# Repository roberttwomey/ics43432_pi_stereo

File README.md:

# ics43432_pi_stereo
stereo i2s mems mic for raspberry pi using ics43432

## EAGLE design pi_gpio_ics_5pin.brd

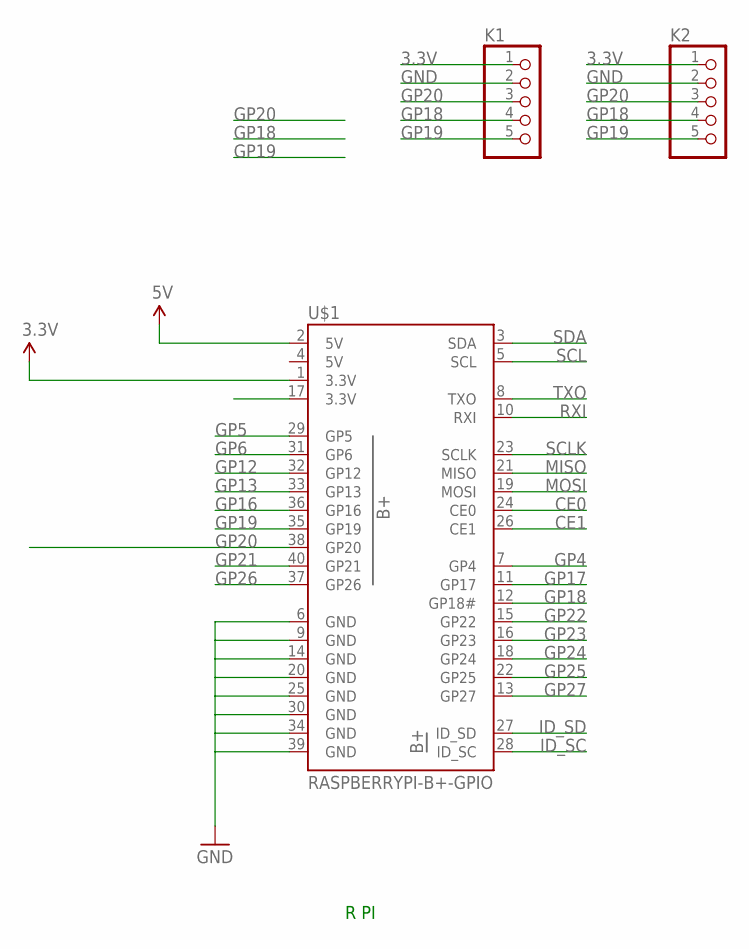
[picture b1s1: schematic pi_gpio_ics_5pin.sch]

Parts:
K1, K2: HEADER-1X5SMT; 1X05_SMT
U$1: RASPBERRYPI-B+-GPIO; 2X20-SHROUDED

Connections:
3.3V: K1.1, K2.1, U$1.1 (3.3V), U$1.17 (3.3V)
5V: U$1.2 (5V), U$1.4 (5V)
CE0: U$1.24 (CE0)
CE1: U$1.26 (CE1)
GND: K1.2, K2.2, U$1.6 (GND), U$1.9 (GND), U$1.14 (GND), U$1.20 (GND), U$1.25 (GND), U$1.30 (GND), U$1.34 (GND), U$1.39 (GND)
GP4: U$1.7 (GP4)
GP5: U$1.29 (GP5)
GP6: U$1.31 (GP6)
GP12: U$1.32 (GP12)
GP13: U$1.33 (GP13)
GP16: U$1.36 (GP16)
GP17: U$1.11 (GP17)
GP18: K1.4, K2.4, U$1.12 (GP18#)
GP19: K1.5, K2.5, U$1.35 (GP19)
GP20: K1.3, K2.3, U$1.38 (GP20)
GP21: U$1.40 (GP21)
GP22: U$1.15 (GP22)
GP23: U$1.16 (GP23)
GP24: U$1.18 (GP24)
GP25: U$1.22 (GP25)
GP26: U$1.37 (GP26)
GP27: U$1.13 (GP27)
ID_SC: U$1.28 (ID_SC)
ID_SD: U$1.27 (ID_SD)
MISO: U$1.21 (MISO)
MOSI: U$1.19 (MOSI)
RXI: U$1.10 (RXI)
SCL: U$1.5 (SCL)
SCLK: U$1.23 (SCLK)
SDA: U$1.3 (SDA)
TXO: U$1.8 (TXO)

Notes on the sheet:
R PI

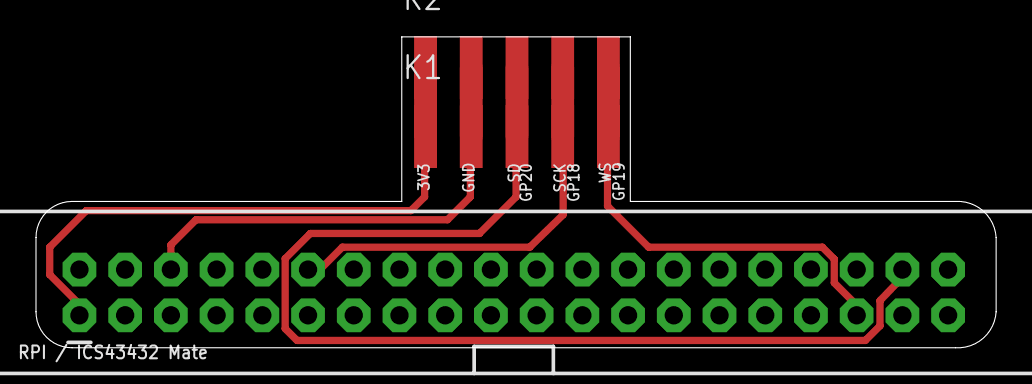
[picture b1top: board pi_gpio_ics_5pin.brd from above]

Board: 2 copper layers, 53.3 x 17.3 mm, 3 parts (0 on the bottom side), 6 nets.

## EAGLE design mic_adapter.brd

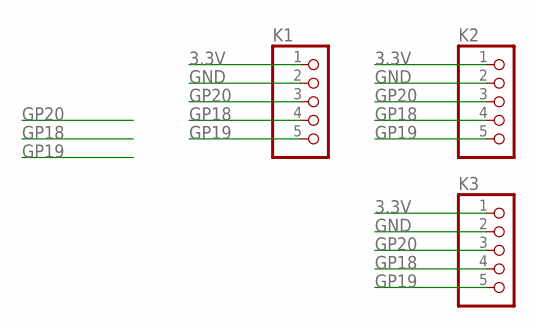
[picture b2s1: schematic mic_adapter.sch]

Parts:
K1, K2, K3: HEADER-1X5SMT; 1X05_SMT

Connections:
3.3V: K1.1, K2.1, K3.1
GND: K1.2, K2.2, K3.2
GP18: K1.4, K2.4, K3.4
GP19: K1.5, K2.5, K3.5
GP20: K1.3, K2.3, K3.3

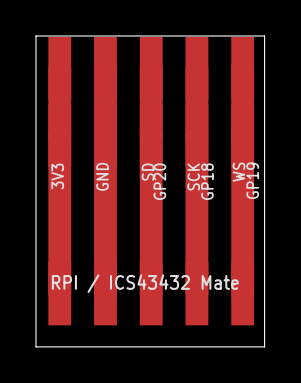
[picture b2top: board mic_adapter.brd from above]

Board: 2 copper layers, 12.7 x 17.3 mm, 3 parts (0 on the bottom side), 5 nets.

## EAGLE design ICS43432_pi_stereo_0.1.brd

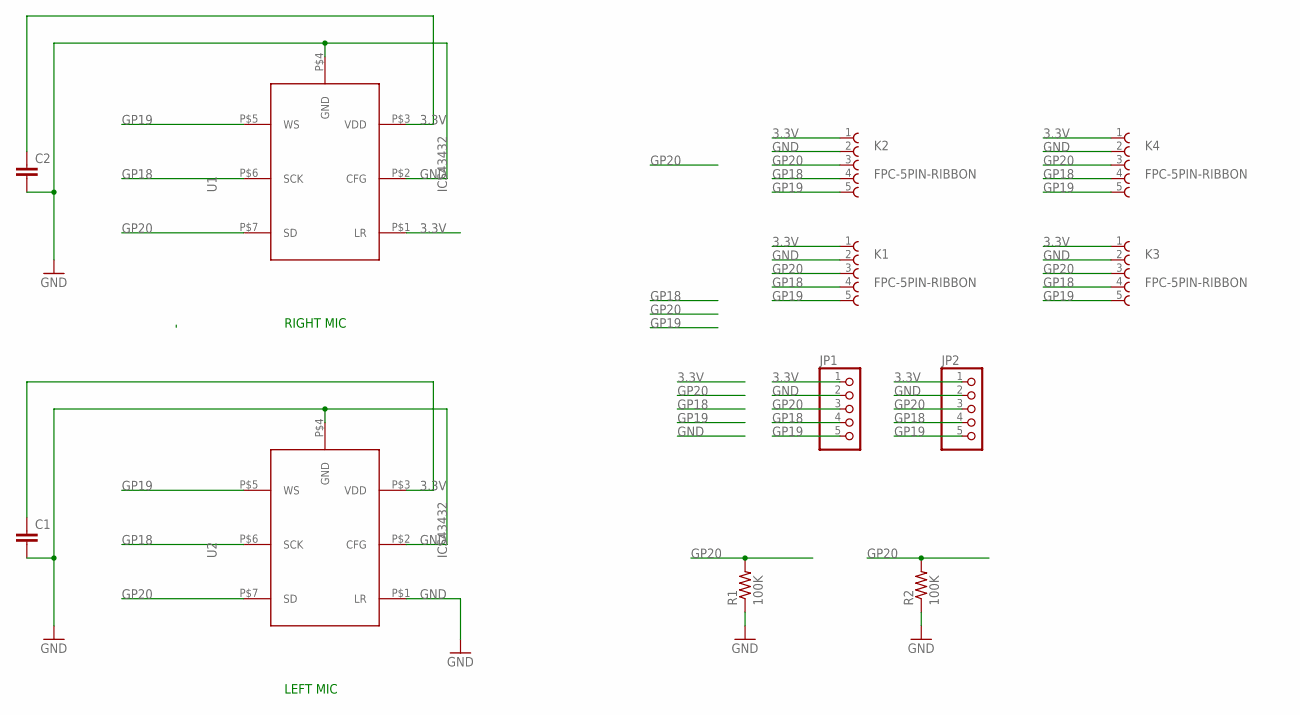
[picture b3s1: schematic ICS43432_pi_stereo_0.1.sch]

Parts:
C1, C2: CAP0402-CAP; 0402-CAP
JP1, JP2: HEADER-1X5ROUND; 1X05_ROUND
K1, K2, K3, K4: FPC-5PIN-RIBBON; 5PIN_FPC
R1, R2: 100K; 0402-RES
U1, U2: ICS43432

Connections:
3.3V: C1.1, C2.1, JP1.1, JP2.1, K1.1, K2.1, K3.1, K4.1, U1.P$1 (LR), U1.P$3 (VDD), U2.P$3 (VDD)
GND: C1.2, C2.2, JP1.2, JP2.2, K1.2, K2.2, K3.2, K4.2, R1.1, R2.1, U1.P$2 (CFG), U1.P$4 (GND), U2.P$1 (LR), U2.P$2 (CFG), U2.P$4 (GND)
GP18: JP1.4, JP2.4, K1.4, K2.4, K3.4, K4.4, U1.P$6 (SCK), U2.P$6 (SCK)
GP19: JP1.5, JP2.5, K1.5, K2.5, K3.5, K4.5, U1.P$5 (WS), U2.P$5 (WS)
GP20: JP1.3, JP2.3, K1.3, K2.3, K3.3, K4.3, R1.2, R2.2, U1.P$7 (SD), U2.P$7 (SD)

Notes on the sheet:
LEFT MIC
RIGHT MIC

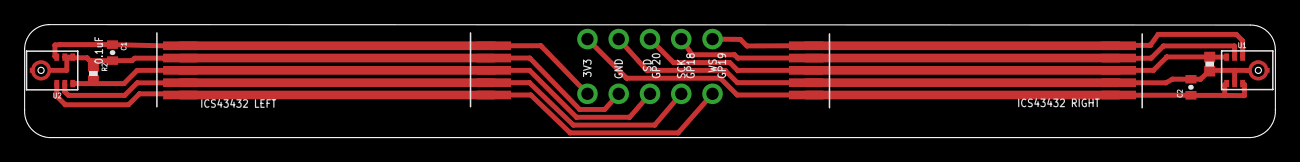
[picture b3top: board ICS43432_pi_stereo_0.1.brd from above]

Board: 2 copper layers, 101.6 x 9.2 mm, 12 parts (0 on the bottom side), 5 nets.

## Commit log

2017-01-07 added photos of assembled circuits

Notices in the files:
parts and their libraries:
SparkFun-Capacitors: Licensing: Creative Commons ShareAlike 4.0 International - https://creativecommons.org/licenses/by-sa/4.0
microbuilder: This work is placed in the public domain, and may be freely used for commercial and non-commercial work with the following conditions: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
